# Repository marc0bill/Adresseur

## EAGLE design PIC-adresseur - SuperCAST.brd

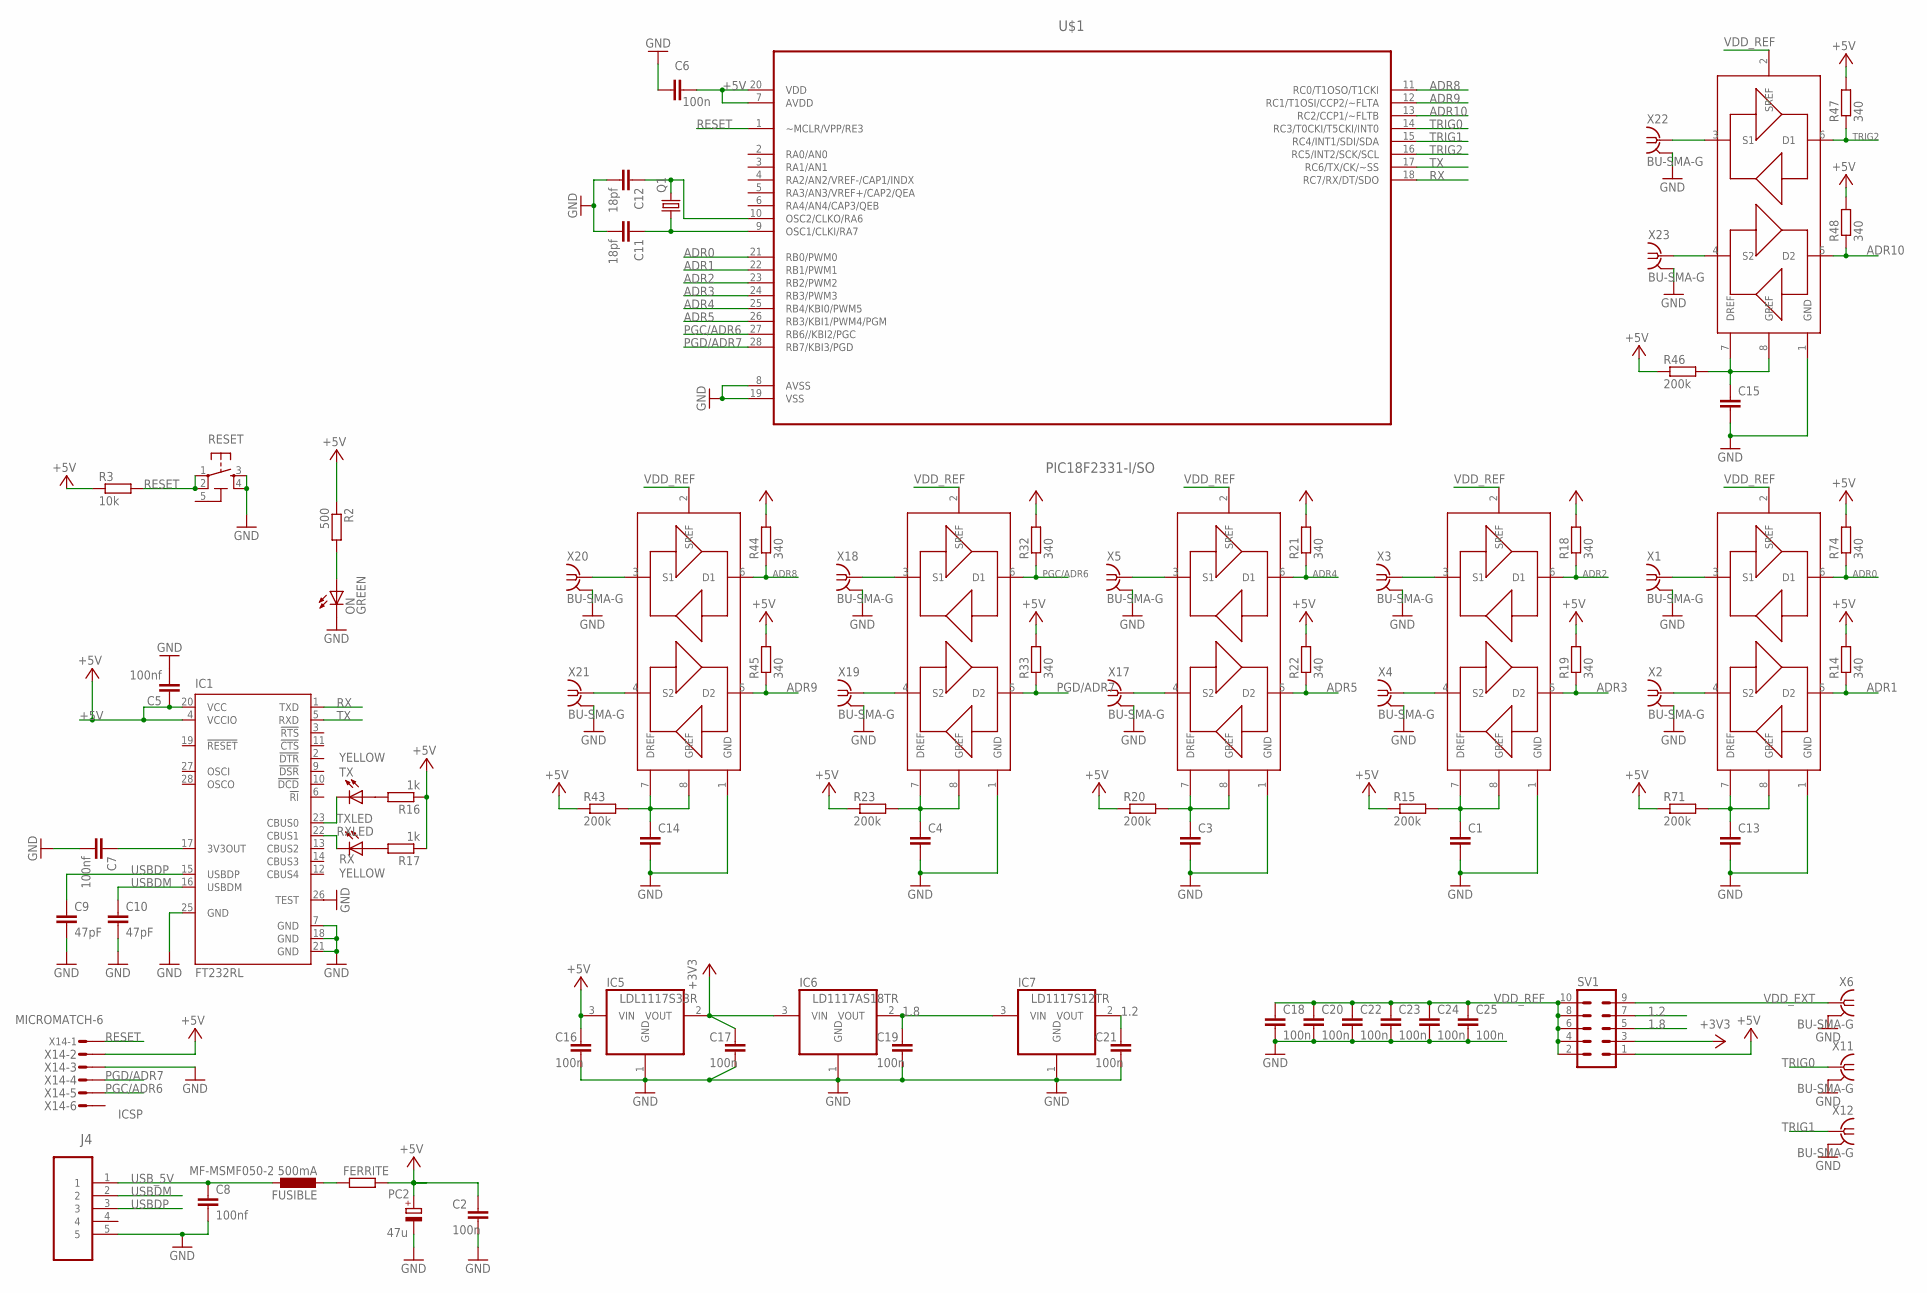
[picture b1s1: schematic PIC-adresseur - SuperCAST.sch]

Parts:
C1, C3, C4, C13, C14, C15: C-EUC0603; C0603
C2, C16, C17, C19, C21: 100n; C0603-ROUND
C5, C7, C8: 100nf; C0603
C6: 100n; C0603K
C9, C10: 47pF; C0603
C11, C12: 18pf; C0603
C18, C20, C22, C23, C24, C25: 100n; C0603
FERRITE: R-EU_M0805; M0805
FUSIBLE: MF-MSMF050-2 500mA; L1812
IC1: FT232RL; SSOP28
IC5: LDL1117S33R; SOT223
IC6: LD1117AS18TR; SOT223
IC7: LD1117S12TR; SOT223
J4: 47346-0001; MOLEX_47346-0001
LV_LVLC1, LV_LVLC2, LV_LVLC3, LV_LVLC4, LV_LVLC5, LV_LVLC6: GTL2002DP_118
ON: GREEN; CHIP-LED0805
PC2: 47u; PANASONIC_D
Q1: CRYSTALSM49; SM49
R2: 500; R0603
R3: 10k; R0603
R14, R18, R19, R21, R22, R32, R33, R44, R45, R47, R48, R74: 340; R0603
R15, R20, R23, R43, R46, R71: 200k; R0603
R16, R17: 1k; R0603
RESET: TS42031-160R-TR-7260; TS42
RX: YELLOW; CHIP-LED0805
SV1: MA05-2
TX: YELLOW; CHIP-LED0805
U$1: PIC18F2331-I/SO; SOIC127P1030X265-28N
X1, X2, X3, X4, X5, X6, X11, X12, X17, X18, X19, X20, X21, X22, X23: BU-SMA-G
X14: MICROMATCH-6

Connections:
1.2: C21.2, IC7.2 (VOUT), SV1.7
1.8: C19.2, IC6.2 (VOUT), IC7.3 (VIN), SV1.5
5-GND: RESET.5 (5-GND)
+3V3: C17.2, IC5.2 (VOUT), IC6.3 (VIN), SV1.3
+5V: C2.2, C5.1, C6.2, C16.2, FERRITE.2, IC1.4 (VCCIO), IC1.20 (VCC), IC5.3 (VIN), PC2.+, R2.1, R3.1, R14.2, R15.1, R16.1, R17.1, R18.2, R19.2, R20.1, R21.2, R22.2, R23.1, R32.2, R33.2, R43.1, R44.2, R45.2, R46.1, R47.2, R48.2, R71.1, R74.2, SV1.1, U$1.7 (AVDD), U$1.20 (VDD), X14.2
ADR0: LV_LVLC2.6 (D1), R74.1, U$1.21 (RB0/PWM0)
ADR0OUT: LV_LVLC2.3 (S1), X1.1
ADR1: LV_LVLC2.5 (D2), R14.1, U$1.22 (RB1/PWM1)
ADR1OUT: LV_LVLC2.4 (S2), X2.1
ADR2: LV_LVLC1.6 (D1), R18.1, U$1.23 (RB2/PWM2)
ADR2OUT: LV_LVLC1.3 (S1), X3.1
ADR3: LV_LVLC1.5 (D2), R19.1, U$1.24 (RB3/PWM3)
ADR3OUT: LV_LVLC1.4 (S2), X4.1
ADR4: LV_LVLC3.6 (D1), R21.1, U$1.25 (RB4/KBI0/PWM5)
ADR4OUT: LV_LVLC3.3 (S1), X5.1
ADR5: LV_LVLC3.5 (D2), R22.1, U$1.26 (RB3/KBI1/PWM4/PGM)
ADR5OUT: LV_LVLC3.4 (S2), X17.1
ADR6OUT: LV_LVLC4.3 (S1), X18.1
ADR7OUT: LV_LVLC4.4 (S2), X19.1
ADR8: LV_LVLC5.6 (D1), R44.1, U$1.11 (RC0/T1OSO/T1CKI)
ADR8OUT: LV_LVLC5.3 (S1), X20.1
ADR9: LV_LVLC5.5 (D2), R45.1, U$1.12 (RC1/T1OSI/CCP2/~FLTA)
ADR9OUT: LV_LVLC5.4 (S2), X21.1
ADR10: LV_LVLC6.5 (D2), R48.1, U$1.13 (RC2/CCP1/~FLTB)
ADR10OUT: LV_LVLC6.4 (S2), X23.1
GND: C1.2, C2.1, C3.2, C4.2, C5.2, C6.1, C7.2, C8.2, C9.2, C10.2, C11.2, C12.2, C13.2, C14.2, C15.2, C16.1, C17.1, C18.2, C19.1, C20.2, C21.1, C22.2, C23.2, C24.2, C25.2, IC1.7 (GND), IC1.18 (GND), IC1.21 (GND), IC1.25 (GND), IC1.26 (TEST), IC5.1 (GND), IC6.1 (GND), IC7.1 (GND), J4.5, LV_LVLC1.1 (GND), LV_LVLC2.1 (GND), LV_LVLC3.1 (GND), LV_LVLC4.1 (GND), LV_LVLC5.1 (GND), LV_LVLC6.1 (GND), ON.C, PC2.-, RESET.3, RESET.4, U$1.8 (AVSS), U$1.19 (VSS), X1.2, X1.3 (2), X1.4 (2), X1.5 (2), X2.2, X2.3 (2), X2.4 (2), X2.5 (2), X3.2, X3.3 (2), X3.4 (2), X3.5 (2), X4.2, X4.3 (2), X4.4 (2), X4.5 (2), X5.2, X5.3 (2), X5.4 (2), X5.5 (2), X6.2, X6.3 (2), X6.4 (2), X6.5 (2), X11.2, X11.3 (2), X11.4 (2), X11.5 (2), X12.2, X12.3 (2), X12.4 (2), X12.5 (2), X14.3, X17.2, X17.3 (2), X17.4 (2), X17.5 (2), X18.2, X18.3 (2), X18.4 (2), X18.5 (2), X19.2, X19.3 (2), X19.4 (2), X19.5 (2), X20.2, X20.3 (2), X20.4 (2), X20.5 (2), X21.2, X21.3 (2), X21.4 (2), X21.5 (2), X22.2, X22.3 (2), X22.4 (2), X22.5 (2), X23.2, X23.3 (2), X23.4 (2), X23.5 (2)
unnamed: ON.A, R2.2
unnamed: C7.1, IC1.17 (3V3OUT)
unnamed: C1.1, LV_LVLC1.7 (DREF), LV_LVLC1.8 (GREF), R15.2
unnamed: FERRITE.1, FUSIBLE.2
unnamed: C3.1, LV_LVLC3.7 (DREF), LV_LVLC3.8 (GREF), R20.2
unnamed: C4.1, LV_LVLC4.7 (DREF), LV_LVLC4.8 (GREF), R23.2
unnamed: C14.1, LV_LVLC5.7 (DREF), LV_LVLC5.8 (GREF), R43.2
unnamed: R17.2, RX.A
unnamed: R16.2, TX.A
unnamed: C15.1, LV_LVLC6.7 (DREF), LV_LVLC6.8 (GREF), R46.2
unnamed: C13.1, LV_LVLC2.7 (DREF), LV_LVLC2.8 (GREF), R71.2
PGC/ADR6: LV_LVLC4.6 (D1), R32.1, U$1.27 (RB6//KBI2/PGC), X14.5
PGD/ADR7: LV_LVLC4.5 (D2), R33.1, U$1.28 (RB7/KBI3/PGD), X14.4
RESET: R3.2, RESET.1, RESET.2, U$1.1 (~MCLR/VPP/RE3), X14.1
RX: IC1.1 (TXD), U$1.18 (RC7/RX/DT/SDO)
RXLED: IC1.22 (CBUS1), RX.C
TRIG0: U$1.14 (RC3/T0CKI/T5CKI/INT0), X11.1
TRIG1: U$1.15 (RC4/INT1/SDI/SDA), X12.1
TRIG2: LV_LVLC6.6 (D1), R47.1, U$1.16 (RC5/INT2/SCK/SCL)
TRIG2OUT: LV_LVLC6.3 (S1), X22.1
TX: IC1.5 (RXD), U$1.17 (RC6/TX/CK/~SS)
TXLED: IC1.23 (CBUS0), TX.C
USBDM: C10.1, IC1.16 (USBDM), J4.2
USBDP: C9.1, IC1.15 (USBDP), J4.3
USB_5V: C8.1, FUSIBLE.1, J4.1
VDD_EXT: SV1.9, X6.1
VDD_REF: C18.1, C20.1, C22.1, C23.1, C24.1, C25.1, LV_LVLC1.2 (SREF), LV_LVLC2.2 (SREF), LV_LVLC3.2 (SREF), LV_LVLC4.2 (SREF), LV_LVLC5.2 (SREF), LV_LVLC6.2 (SREF), SV1.2, SV1.4, SV1.6, SV1.8, SV1.10
XTAL1: C12.1, Q1.2, U$1.10 (OSC2/CLKO/RA6)
XTAL2: C11.1, Q1.1, U$1.9 (OSC1/CLKI/RA7)

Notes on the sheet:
ICSP

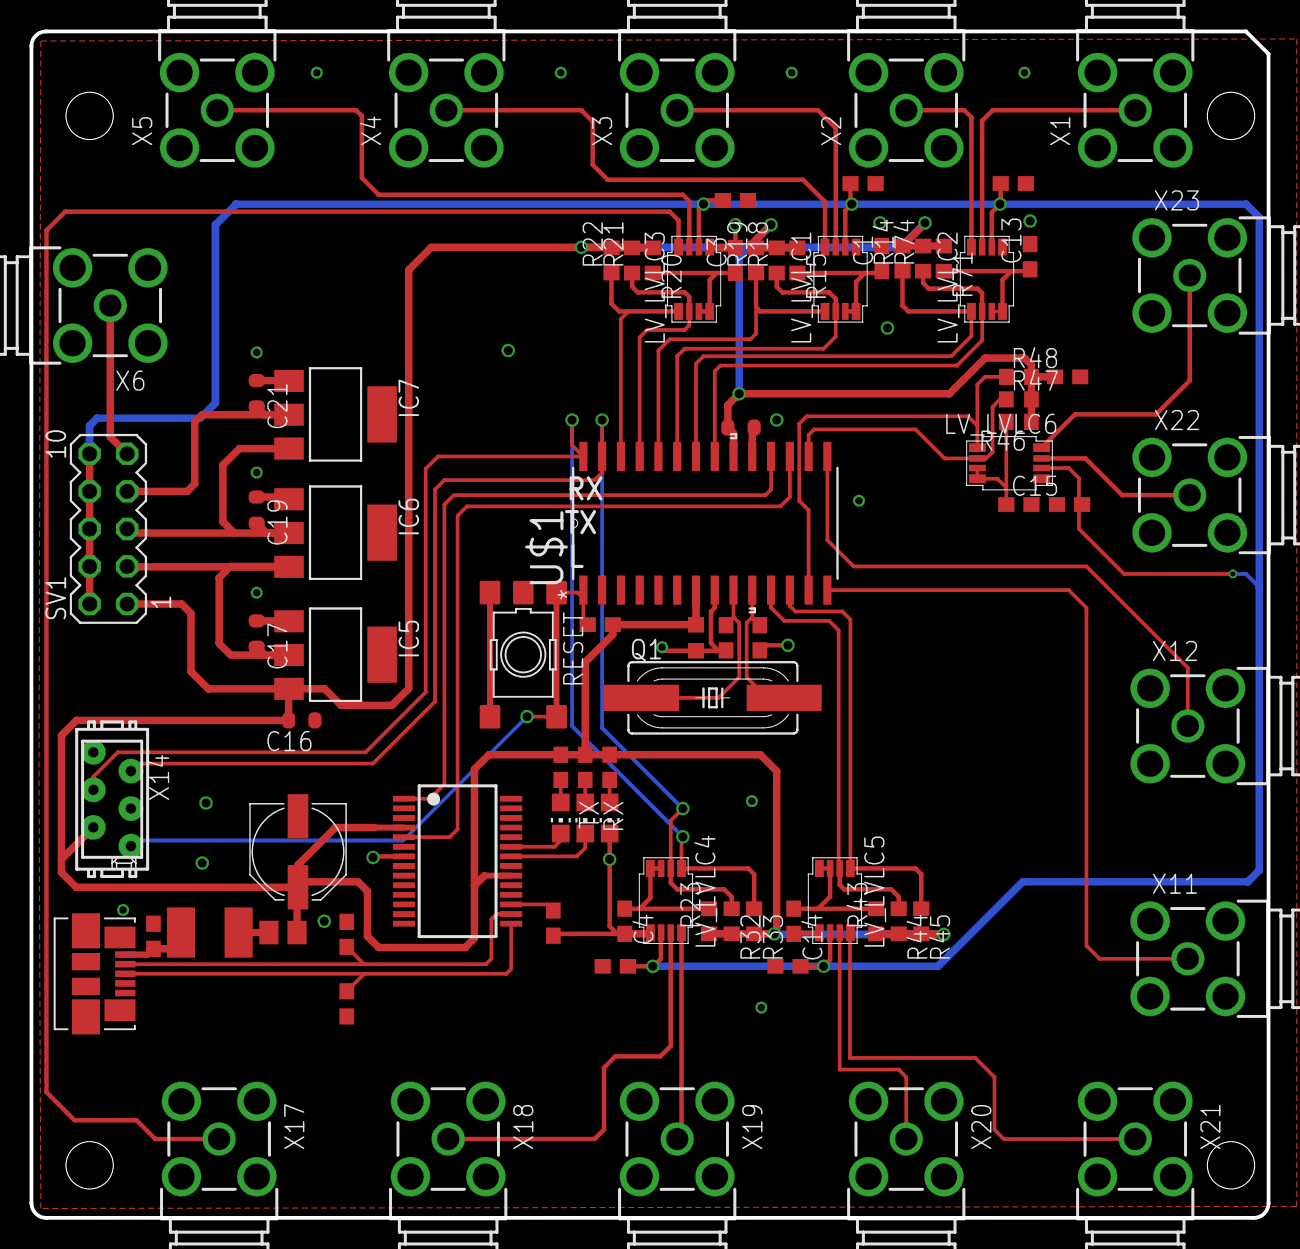
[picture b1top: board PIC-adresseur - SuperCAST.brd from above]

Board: 2 copper layers, 83.7 x 80.3 mm, 84 parts (0 on the bottom side), 54 nets.

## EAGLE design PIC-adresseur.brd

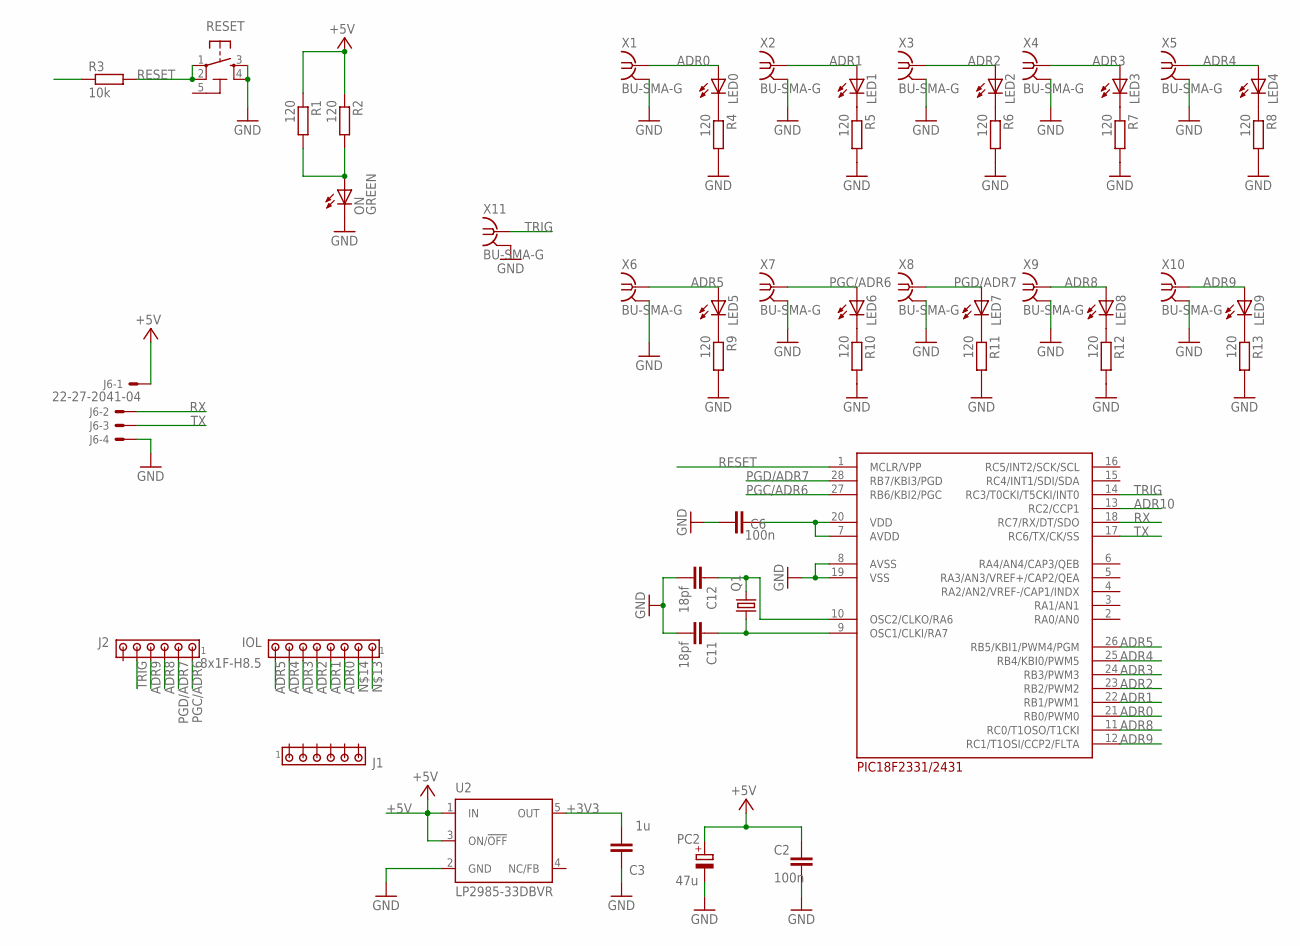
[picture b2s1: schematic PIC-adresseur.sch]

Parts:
C2: 100n; C0603-ROUND
C3: 1u; C0603-ROUND
C6: 100n; C0603K
C11, C12: 18pf; C0603
IOL: 8x1F-H8.5; 10X08MTA
J1, J2: MTA06-100; 10X06MTA
J6: 22-27-2041-04; 6410-04
LED0, LED1, LED2, LED3, LED4, LED5, LED6, LED7, LED8, LED9: LEDCHIP-LED0805; CHIP-LED0805
ON: GREEN; CHIP-LED0805
PC2: 47u; PANASONIC_D
Q1: CRYSTALSM49; SM49
R1, R2, R4, R5, R6, R7, R8, R9, R10, R11, R12, R13: 120; R0805
R3: 10k; R0805
RESET: TS42031-160R-TR-7260; TS42
U2: LP2985-33DBVR; SOT23-DBV
U$2: PIC18F2331/2431; DIL28-3
X1, X2, X3, X4, X5, X6, X7, X8, X9, X10, X11: BU-SMA-G

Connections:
5-GND: RESET.5 (5-GND)
+3V3: C3.2, C6.2, R3.1, U2.5 (OUT), U$2.7 (AVDD), U$2.20 (VDD)
+5V: C2.2, J6.1, PC2.+, R1.1, R2.1, U2.1 (IN), U2.3 (ON/!OFF)
ADR0: IOL.3, LED0.A, U$2.21 (RB0/PWM0), X1.1
ADR1: IOL.4, LED1.A, U$2.22 (RB1/PWM1), X2.1
ADR2: IOL.5, LED2.A, U$2.23 (RB2/PWM2), X3.1
ADR3: IOL.6, LED3.A, U$2.24 (RB3/PWM3), X4.1
ADR4: IOL.7, LED4.A, U$2.25 (RB4/KBI0/PWM5), X5.1
ADR5: IOL.8, LED5.A, U$2.26 (RB5/KBI1/PWM4/PGM), X6.1
ADR8: J2.4 (3), LED8.A, U$2.11 (RC0/T1OSO/T1CKI), X9.1
ADR9: J2.3 (4), LED9.A, U$2.12 (RC1/T1OSI/CCP2/FLTA), X10.1
ADR10: U$2.13 (RC2/CCP1)
GND: C2.1, C3.1, C6.1, C11.2, C12.2, J6.4, ON.C, PC2.-, R4.2, R5.2, R6.2, R7.2, R8.2, R9.2, R10.2, R11.2, R12.2, R13.2, RESET.3, RESET.4, U2.2 (GND), U$2.8 (AVSS), U$2.19 (VSS), X1.2, X1.3 (2), X1.4 (2), X1.5 (2), X2.2, X2.3 (2), X2.4 (2), X2.5 (2), X3.2, X3.3 (2), X3.4 (2), X3.5 (2), X4.2, X4.3 (2), X4.4 (2), X4.5 (2), X5.2, X5.3 (2), X5.4 (2), X5.5 (2), X6.2, X6.3 (2), X6.4 (2), X6.5 (2), X7.2, X7.3 (2), X7.4 (2), X7.5 (2), X8.2, X8.3 (2), X8.4 (2), X8.5 (2), X9.2, X9.3 (2), X9.4 (2), X9.5 (2), X10.2, X10.3 (2), X10.4 (2), X10.5 (2), X11.2, X11.3 (2), X11.4 (2), X11.5 (2)
unnamed: LED0.C, R4.1
unnamed: LED1.C, R5.1
unnamed: ON.A, R1.2, R2.2
unnamed: LED2.C, R6.1
unnamed: LED3.C, R7.1
unnamed: LED4.C, R8.1
unnamed: LED5.C, R9.1
unnamed: LED6.C, R10.1
unnamed: LED7.C, R11.1
unnamed: LED8.C, R12.1
unnamed: LED9.C, R13.1
PGC/ADR6: J2.6 (1), LED6.A, U$2.27 (RB6/KBI2/PGC), X7.1
PGD/ADR7: J2.5 (2), LED7.A, U$2.28 (RB7/KBI3/PGD), X8.1
RESET: R3.2, RESET.1, RESET.2, U$2.1 (MCLR/VPP)
RX: J6.2, U$2.18 (RC7/RX/DT/SDO)
TRIG: J2.2 (5), U$2.14 (RC3/T0CKI/T5CKI/INT0), X11.1
TX: J6.3, U$2.17 (RC6/TX/CK/SS)
XTAL1: C12.1, Q1.2, U$2.10 (OSC2/CLKO/RA6)
XTAL2: C11.1, Q1.1, U$2.9 (OSC1/CLKI/RA7)

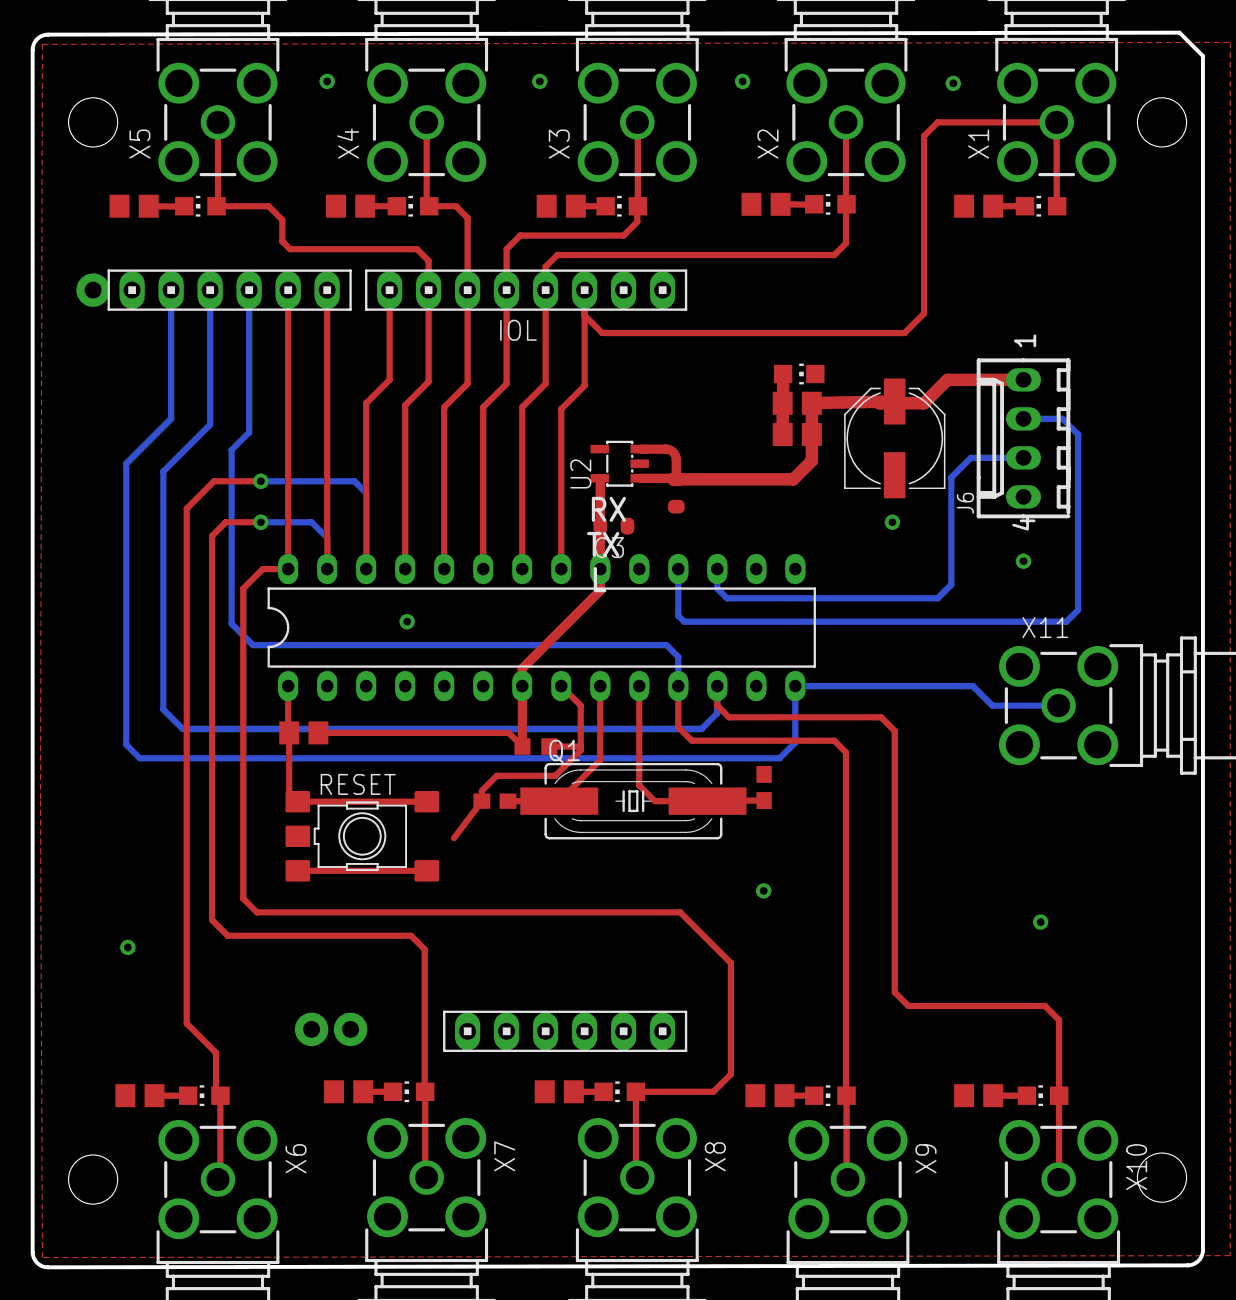
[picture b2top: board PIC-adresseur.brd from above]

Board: 2 copper layers, 76.2 x 80.4 mm, 49 parts (0 on the bottom side), 30 nets.

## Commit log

2018-02-16 Ajoute description
2018-02-16 Amélioration de convertion ASCII pour Tx
2018-02-16 Passage à 16MHz
2018-02-22 Debug firmware
    Patch all bug \o/
2018-02-22 Add .hex
2018-05-29 modif
2020-06-30 Adresseur SuperCAST v0.1
2021-01-07 Adresseur SuperCAST v0.2
